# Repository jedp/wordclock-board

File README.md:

## Notes

### STM32F04

Programmed via ST-Link (CLK, GND, DIO, NRST). Easy peasy!

External low-speed crystal oscillator (32.768kHz) enables real-time clock
module to function on VBAT when VDD is disconnected.

### MAX7129

Imagine the 64 LEDs are 8 7-segment LEDs.

Pin 1 DATA: Data loaded on CLK's rising edge.

Pin 12 NCS: Data is loaded into the shift register when this is low.

Pin 13 CLK.

Pins 2, 3, 5, 6, 7, 8, 10, and 11 (the DIG pins) are pulled high when
switched off.

Pins 14, 15, 16, 17, 20, 21, 22, and 22 (the SEG and DP pins) are pulled low when
switched off.

Note that peak current is set with an external resistor on pin 18 (R1). The
datasheet has a section on how to select the correct resistor value. Note that
you need to do this whether or not you use the `intensity` configuration,
because the MAX7219 will power up into a test mode with all LEDs blazing
*before* your configurations takes effect. You could probably burn out your
nice display by accident this way. So you can tweak the 10k resistor on R1, but
don't jump it.

### Other assorted components

MCP1802: LDO voltage regulator (5V to 3V3).

USBLC6: ESD protection on the USB interface.

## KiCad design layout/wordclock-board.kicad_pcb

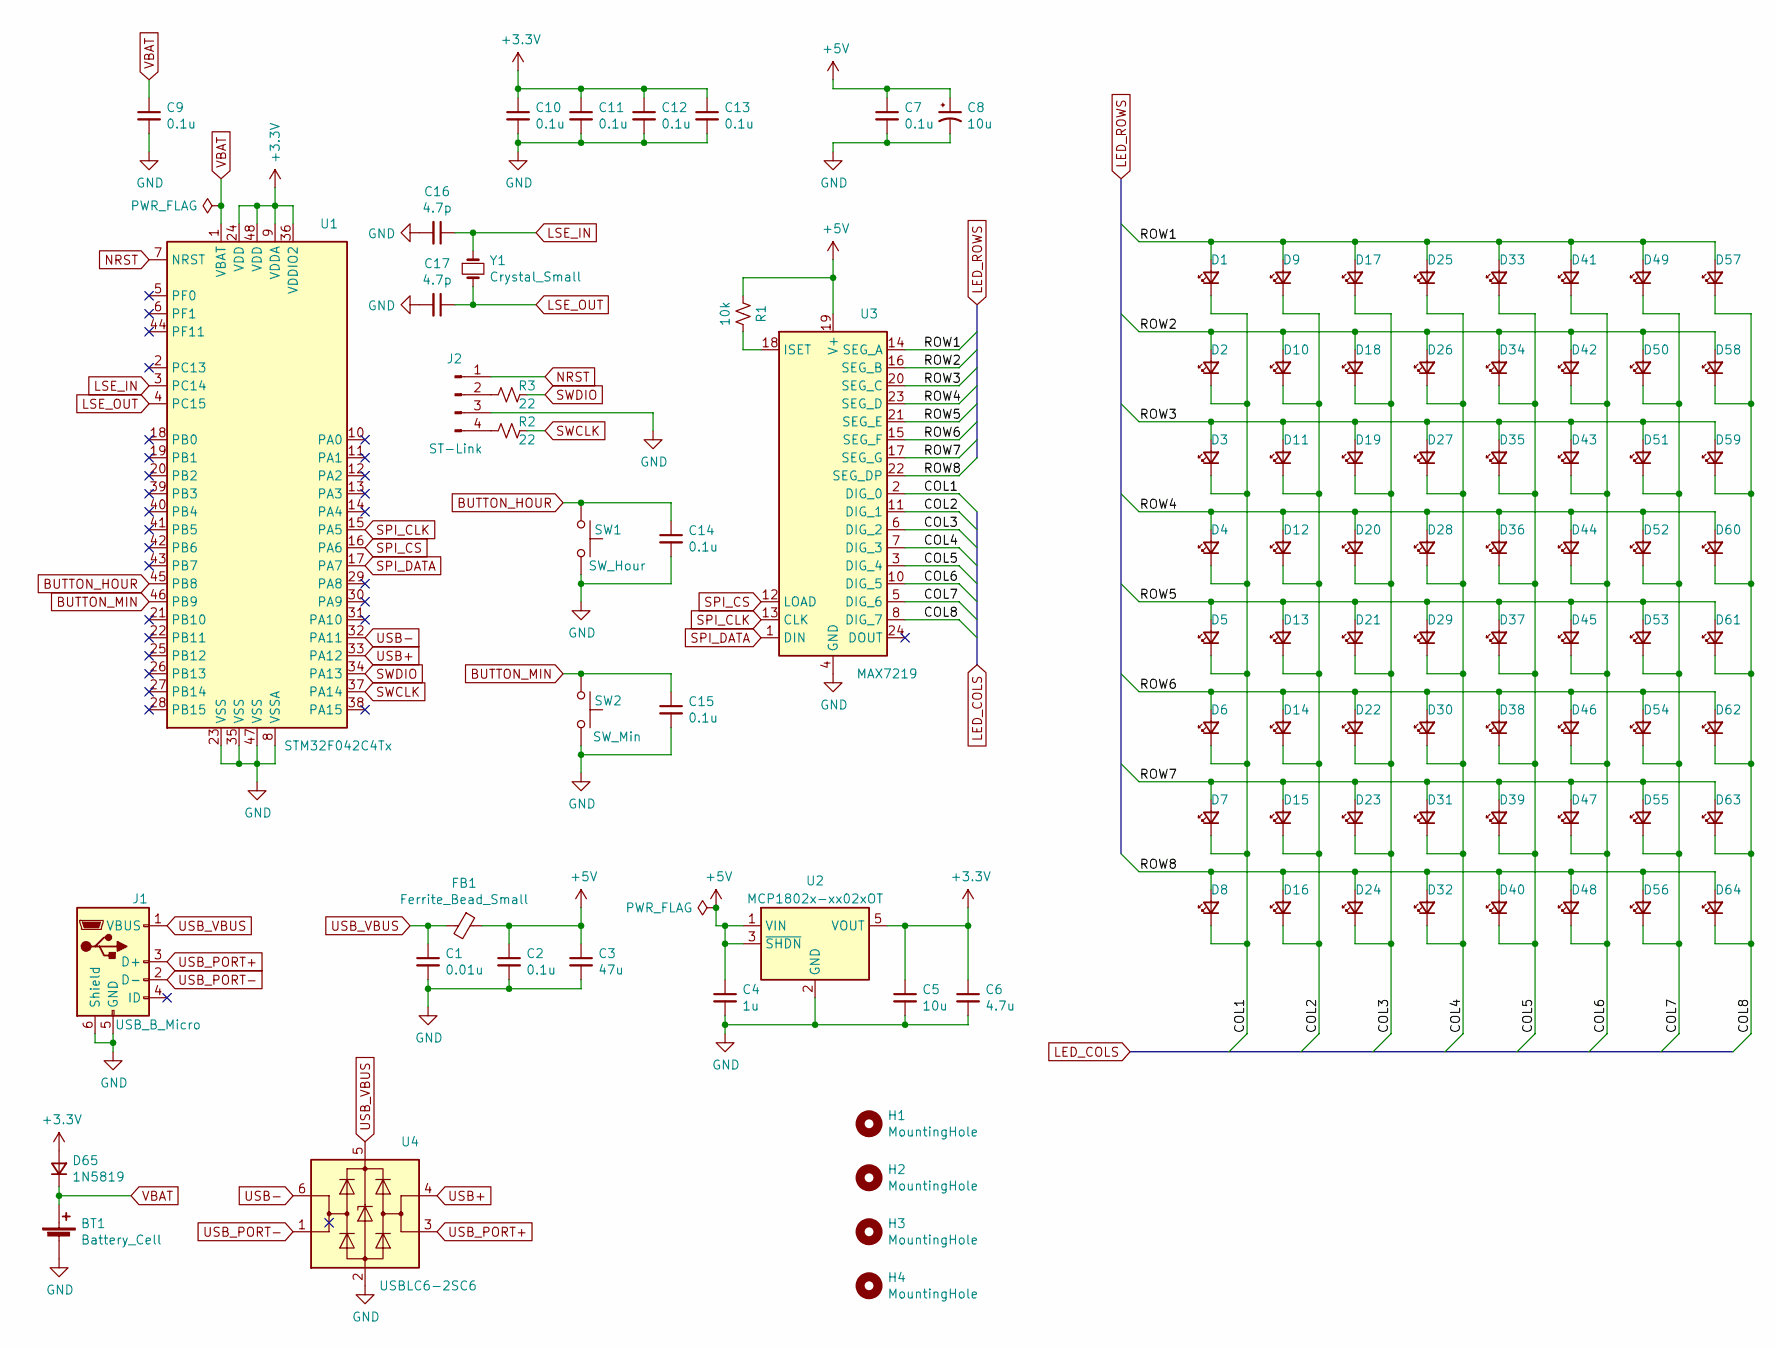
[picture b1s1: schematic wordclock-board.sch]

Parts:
BT1: Battery_Cell; BatteryHolder_Seiko_MS621F
C1: 0.01u; C_0603_1608Metric
C2, C7, C9, C10, C11, C12, C13: 0.1u; C_0603_1608Metric
C3: 47u; C_0805_2012Metric
C4: 1u; C_0603_1608Metric
C5: 10u; C_0805_2012Metric
C6: 4.7u; C_0805_2012Metric
C8: 10u; CP_Elec_5x4.5
C14, C15: 0.1u; C_0805_2012Metric
C16, C17: 4.7p; C_0603_1608Metric
D1, D2, D3, D4, D5, D6, D7, D8, D9, D10, D11, D12, D13, D14, D15, D16, D17, D18, D19, D20, D21, D22, D23, D24, D25, D26, D27, D28, D29, D30, D31, D32, D33, D34, D35, D36, D37, D38, D39, D40, D41, D42, D43, D44, D45, D46, D47, D48, D49, D50, D51, D52, D53, D54, D55, D56, D57, D58, D59, D60, D61, D62, D63, D64: LED_Small; LED_0603_1608Metric
D65: 1N5819; D_0805_2012Metric
FB1: Ferrite_Bead_Small; L_0805_2012Metric
H1, H2, H3, H4: MountingHole; MountingHole_3.2mm_M3
J1: USB_B_Micro; USB_Micro-B_Molex-105133-0001
J2: ST-Link; PinHeader_1x04_P2.54mm_Vertical
R1: 10k; R_0603_1608Metric
R2, R3: 22; R_0603_1608Metric
SW1: SW_Hour; SW_Tactile_SPST_Angled_PTS645Vx83-2LFS
SW2: SW_Min; SW_Tactile_SPST_Angled_PTS645Vx83-2LFS
U1: STM32F042C4Tx; LQFP-48_7x7mm_P0.5mm
U2: MCP1802x-xx02xOT; SOT-23-5
U3: MAX7219; SOIC-24W_7.5x15.4mm_P1.27mm
U4: USBLC6-2SC6; SOT-23-6
Y1: Crystal_Small; Crystal_SMD_MicroCrystal_CC5V-T1A-2Pin_4.1x1.5mm_HandSolder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

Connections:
+3V3: C5.1, C6.1, C10.1, C11.1, C12.1, C13.1, D65.2 (A), U1.9 (VDDA), U1.24 (VDD), U1.36 (VDDIO2), U1.48 (VDD), U2.5 (VOUT)
+5V: C2.1, C3.1, C4.1, C7.1, C8.1, FB1.1, R1.2, U2.1 (VIN), U2.3 (~SHDN), U3.19 (V+)
/COL1: D1.1 (K), D2.1 (K), D3.1 (K), D4.1 (K), D5.1 (K), D6.1 (K), D7.1 (K), D8.1 (K), U3.2 (DIG_0)
/COL2: D9.1 (K), D10.1 (K), D11.1 (K), D12.1 (K), D13.1 (K), D14.1 (K), D15.1 (K), D16.1 (K), U3.11 (DIG_1)
/COL3: D17.1 (K), D18.1 (K), D19.1 (K), D20.1 (K), D21.1 (K), D22.1 (K), D23.1 (K), D24.1 (K), U3.6 (DIG_2)
/COL4: D25.1 (K), D26.1 (K), D27.1 (K), D28.1 (K), D29.1 (K), D30.1 (K), D31.1 (K), D32.1 (K), U3.7 (DIG_3)
/COL5: D33.1 (K), D34.1 (K), D35.1 (K), D36.1 (K), D37.1 (K), D38.1 (K), D39.1 (K), D40.1 (K), U3.3 (DIG_4)
/COL6: D41.1 (K), D42.1 (K), D43.1 (K), D44.1 (K), D45.1 (K), D46.1 (K), D47.1 (K), D48.1 (K), U3.10 (DIG_5)
/COL7: D49.1 (K), D50.1 (K), D51.1 (K), D52.1 (K), D53.1 (K), D54.1 (K), D55.1 (K), D56.1 (K), U3.5 (DIG_6)
/COL8: D57.1 (K), D58.1 (K), D59.1 (K), D60.1 (K), D61.1 (K), D62.1 (K), D63.1 (K), D64.1 (K), U3.8 (DIG_7)
/ROW1: D1.2 (A), D9.2 (A), D17.2 (A), D25.2 (A), D33.2 (A), D41.2 (A), D49.2 (A), D57.2 (A), U3.14 (SEG_A)
/ROW2: D2.2 (A), D10.2 (A), D18.2 (A), D26.2 (A), D34.2 (A), D42.2 (A), D50.2 (A), D58.2 (A), U3.16 (SEG_B)
/ROW3: D3.2 (A), D11.2 (A), D19.2 (A), D27.2 (A), D35.2 (A), D43.2 (A), D51.2 (A), D59.2 (A), U3.20 (SEG_C)
/ROW4: D4.2 (A), D12.2 (A), D20.2 (A), D28.2 (A), D36.2 (A), D44.2 (A), D52.2 (A), D60.2 (A), U3.23 (SEG_D)
/ROW5: D5.2 (A), D13.2 (A), D21.2 (A), D29.2 (A), D37.2 (A), D45.2 (A), D53.2 (A), D61.2 (A), U3.21 (SEG_E)
/ROW6: D6.2 (A), D14.2 (A), D22.2 (A), D30.2 (A), D38.2 (A), D46.2 (A), D54.2 (A), D62.2 (A), U3.15 (SEG_F)
/ROW7: D7.2 (A), D15.2 (A), D23.2 (A), D31.2 (A), D39.2 (A), D47.2 (A), D55.2 (A), D63.2 (A), U3.17 (SEG_G)
/ROW8: D8.2 (A), D16.2 (A), D24.2 (A), D32.2 (A), D40.2 (A), D48.2 (A), D56.2 (A), D64.2 (A), U3.22 (SEG_DP)
BUTTON_HOUR: C14.1, SW1.1, U1.45 (PB8)
BUTTON_MIN: C15.1, SW2.1, U1.46 (PB9)
GND: BT1.2 (-), C1.2, C2.2, C3.2, C4.2, C5.2, C6.2, C7.2, C8.2, C9.2, C10.2, C11.2, C12.2, C13.2, C14.2, C15.2, C16.2, C17.2, J1.5 (GND), J1.6 (Shield), J2.3, SW1.2, SW2.2, U1.8 (VSSA), U1.23 (VSS), U1.35 (VSS), U1.47 (VSS), U2.2 (GND), U3.4 (GND), U3.9 (GND), U4.2 (GND)
LSE_IN: C16.1, U1.3 (PC14), Y1.1
LSE_OUT: C17.1, U1.4 (PC15), Y1.2
NRST: J2.1, U1.7 (NRST)
unnamed: J2.2, R3.2
unnamed: J2.4, R2.2
unnamed: R1.1, U3.18 (ISET)
SPI_CLK: U1.15 (PA5), U3.13 (CLK)
SPI_CS: U1.16 (PA6), U3.12 (LOAD)
SPI_DATA: U1.17 (PA7), U3.1 (DIN)
SWCLK: R2.1, U1.37 (PA14)
SWDIO: R3.1, U1.34 (PA13)
USB+: U1.33 (PA12), U4.4 (I/O2)
USB-: U1.32 (PA11), U4.6 (I/O1)
USB_PORT+: J1.3 (D+), U4.3 (I/O2)
USB_PORT-: J1.2 (D-), U4.1 (I/O1)
USB_VBUS: C1.1, FB1.2, J1.1 (VBUS), U4.5 (VBUS)
VBAT: BT1.1 (+), C9.1, D65.1 (K), U1.1 (VBAT)

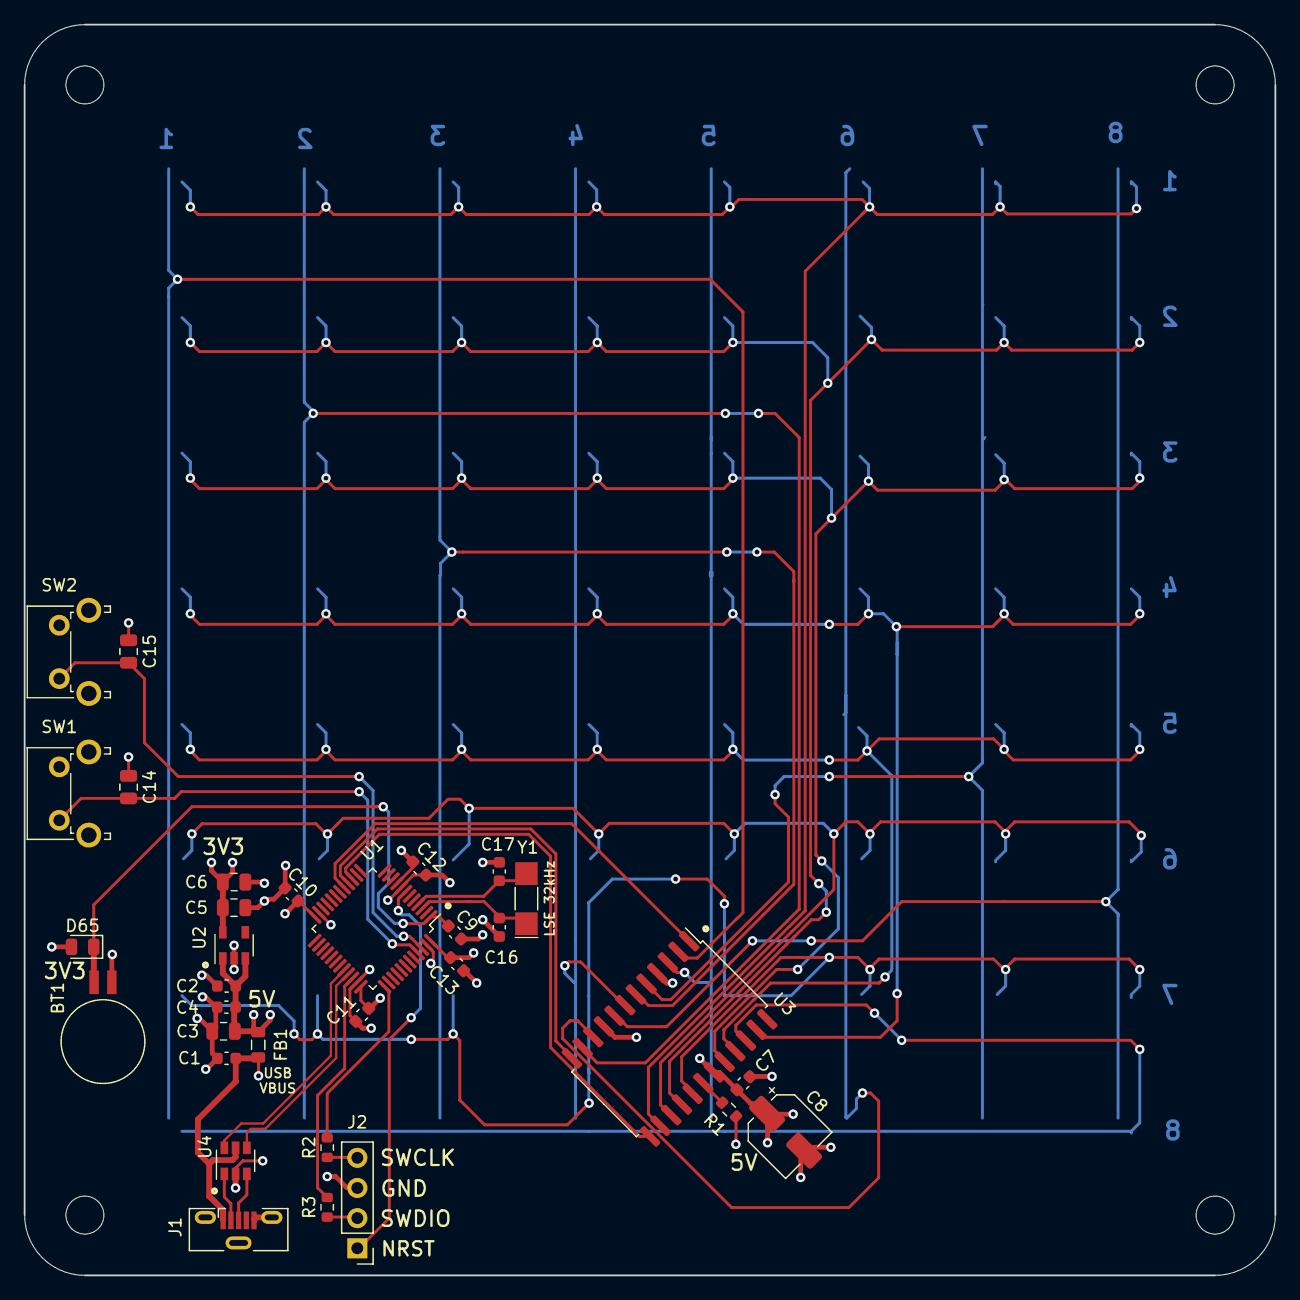
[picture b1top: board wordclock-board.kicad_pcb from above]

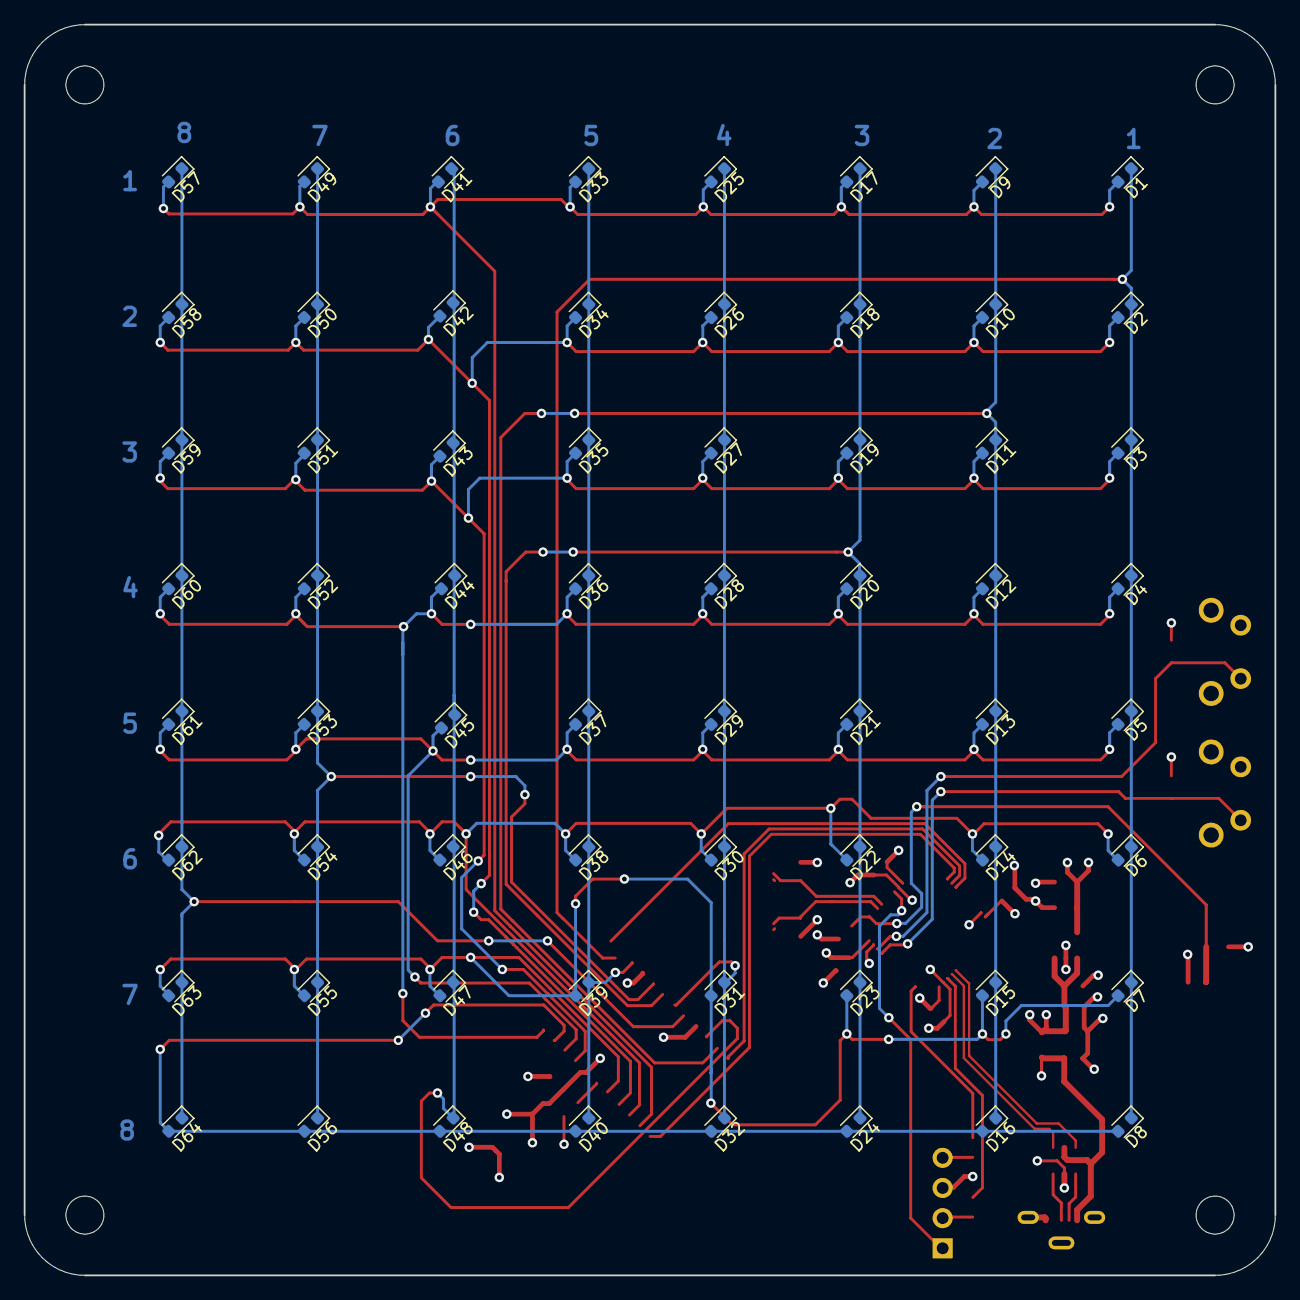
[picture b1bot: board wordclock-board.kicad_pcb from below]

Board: 4 copper layers, 105.4 x 105.4 mm, 100 parts (64 on the bottom side), 38 nets.

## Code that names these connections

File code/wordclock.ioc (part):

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Mcu.Name=STM32F042C(4-6)Tx
Mcu.Package=LQFP48
Mcu.UserName=STM32F042C4Tx
PA11.Mode=Device
PA11.Signal=USB_DM
PA12.Mode=Device
PA12.Signal=USB_DP
PA5.Mode=RX_Only_Simplex_Unidirect_Slave
PA5.Signal=SPI1_SCK
PA6.GPIOParameters=GPIO_Label
PA6.GPIO_Label=SPI1_CS
PA6.Signal=GPIO_Output
PA7.Mode=RX_Only_Simplex_Unidirect_Slave
PA7.Signal=SPI1_MOSI
PB8.GPIOParameters=GPIO_Label
PB8.GPIO_Label=INCR_HOUR
PB8.Signal=GPIO_Input
PB9.GPIOParameters=GPIO_Label
PB9.GPIO_Label=INCR_MIN
PB9.Signal=GPIO_Input
PC14OSC32_IN.Mode=LSE-External-Oscillator
PC14OSC32_IN.Signal=RCC_OSC32_IN
PC15OSC32_OUT.Mode=LSE-External-Oscillator
PC15OSC32_OUT.Signal=RCC_OSC32_OUT
RCC.SYSCLKFreq_VALUE=8000000
board=custom

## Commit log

2021-01-17 wordclock board
2021-01-17 readme
